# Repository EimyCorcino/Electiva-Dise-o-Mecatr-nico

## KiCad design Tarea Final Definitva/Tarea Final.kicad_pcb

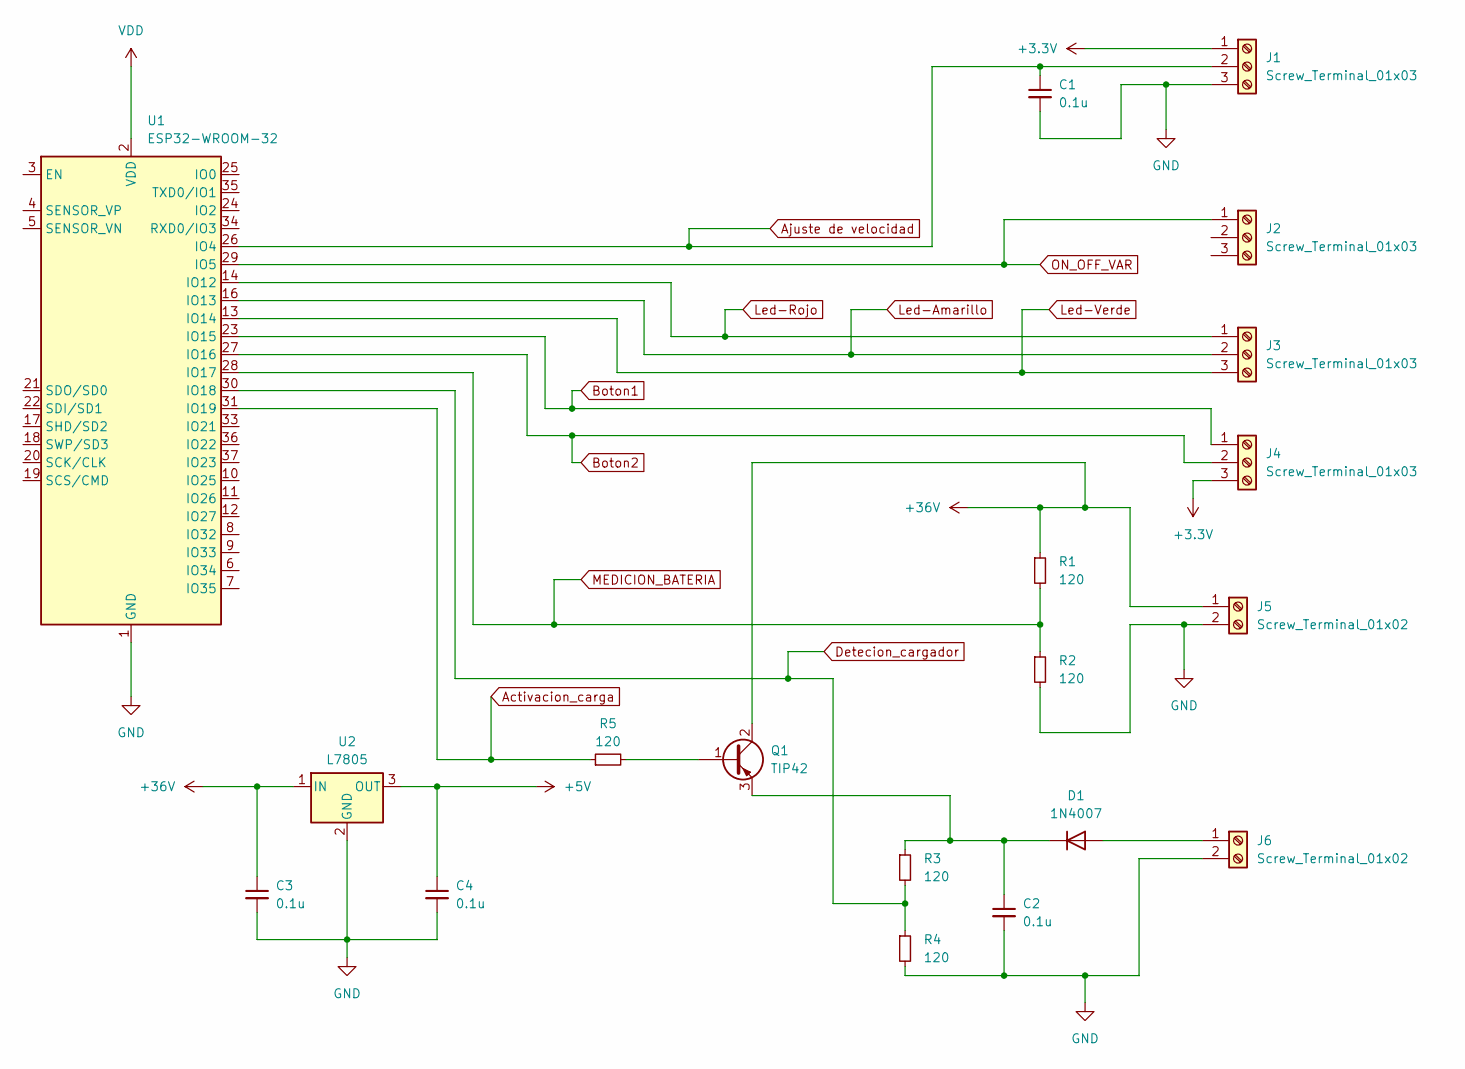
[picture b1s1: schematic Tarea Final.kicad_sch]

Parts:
C1, C2, C3, C4: 0.1u; C_0402_1005Metric
D1: 1N4007; D_DO-41_SOD81_P2.54mm_Vertical_AnodeUp
J1, J2, J3, J4: Screw_Terminal_01x03; TerminalBlock_Xinya_XY308-2.54-3P_1x03_P2.54mm_Horizontal
J5, J6: Screw_Terminal_01x02; TerminalBlock_Xinya_XY308-2.54-2P_1x02_P2.54mm_Horizontal
Q1: TIP42; TO-220-3_Vertical
R1, R2, R3, R4, R5: 120; R_0402_1005Metric
U1: ESP32-WROOM-32
U2: L7805; TO-263-3_TabPin2

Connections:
+3.3V: J1.1, J4.3
+5V: C4.1, U2.3 (OUT)
+36V: C3.1, J5.1, Q1.2 (C), R1.1, U2.1 (IN)
Activacion_carga: R5.1, U1.31 (IO19)
Ajuste de velocidad: C1.1, J1.2, U1.26 (IO4)
Boton1: J4.1, U1.23 (IO15)
Boton2: J4.2, U1.27 (IO16)
Detecion_cargador: R3.2, R4.1, U1.30 (IO18)
GND: C1.2, C2.2, C3.2, C4.2, J1.3, J5.2, J6.2, R2.2, R4.2, U1.1 (GND), U1.15 (GND), U1.38 (GND), U1.39 (GND), U2.2 (GND)
Led-Amarillo: J3.2, U1.16 (IO13)
Led-Rojo: J3.1, U1.14 (IO12)
Led-Verde: J3.3, U1.13 (IO14)
MEDICION_BATERIA: R1.2, R2.1, U1.28 (IO17)
unnamed: D1.2 (A), J6.1
unnamed: C2.1, D1.1 (K), Q1.3 (E), R3.1
unnamed: Q1.1 (B), R5.2
ON_OFF_VAR: J2.1, U1.29 (IO5)
VDD: U1.2 (VDD)

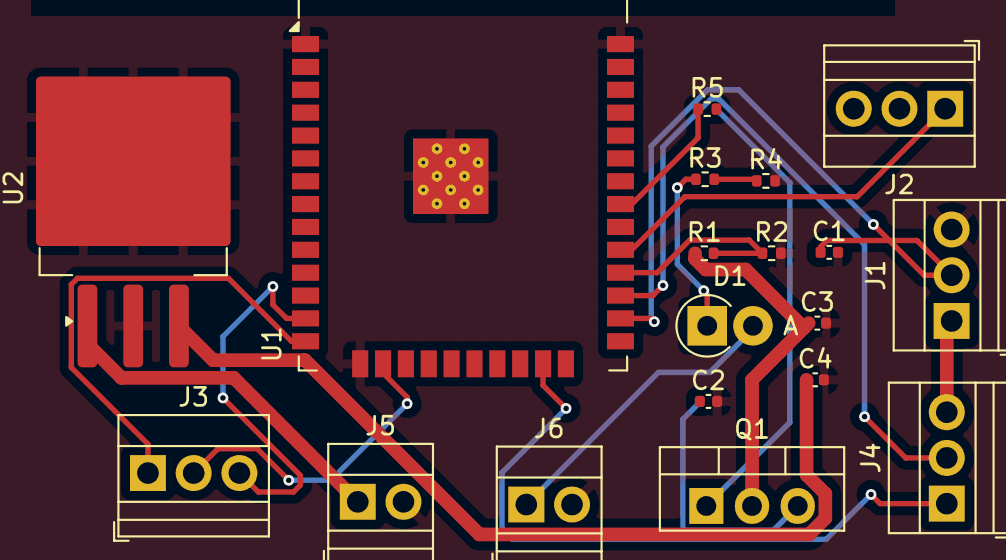
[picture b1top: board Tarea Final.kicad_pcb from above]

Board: 2 copper layers, 19 parts (0 on the bottom side), 17 nets.

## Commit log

2024-10-04 agregabdi carpeta Borradores
2024-10-06 Resumenes
2024-11-09 subiendo la carpeta Modulo NRD24L01
2024-12-07 Create Link del video
